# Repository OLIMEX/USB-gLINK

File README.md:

# USB-gLINK

Industrial grade USB LTE cat 4 module optimized for IoT applications with integrated LiPo Battery power supply charger and Navigation.

Product page: https://www.olimex.com/Products/IoT/LTE/USB-gLINK/open-source-hardware

* Works with OLinuXino OSHW Linux Computers, Beaglebone and Raspberry Pi.

* LTE speed 150Mbps downlink and 50Mbps uplink. Backward-compatible with existing EDGE and GSM/GPRS networks.

* Navigation Supports: GPS, GLONASS, BeiDou/Compass, Galileo and QZSS navigation.

* Protocols: TCP / UDP / PPP / FTP / HTTP / NTP / PING / QMI / NITZ / SMTP / MQTT / CMUX / HTTPS / FTPS / SMTPS / SSL / MMS / FILE.

* USB serial drivers for Windows 7/8/8.1/10, Linux and Android.

* Works anywehere in the world: B1 / B2 / B3 / B4 / B5 / B7 / B8 / B12 / B13 / B18 / B19 / B20 / B25 / B26 / B28 / B38 / B39 / B40 / B41.

* Approvals Carrier: Deutsche Telekom (Europe), Verizon/AT&T/Sprint/U.S. Cellular/T-Mobile (North America), Telus/Rogers (Canada)

* Regulatory: GCF (Global), CE (Europe), FCC/PTCRB (North America), IC (Canada), Anatel (Brazil), IFETEL (Mexico), SRRC/CCC/NAL (China), KC (South Korea), NCC (Taiwan, China), JATE/TELEC (Japan), RCM (Australia & New Zealand), FAC (Russia), NBTC (Thailand), IMDA (Singapore), ICASA (South Africa)

## Licensee
* Hardware is released under CERN Open Hardware Licence Version 2 -
Strongly Reciprocal
* Software is released under GPL3 Licensee
* Documentation is released under CC BY-SA 3.0

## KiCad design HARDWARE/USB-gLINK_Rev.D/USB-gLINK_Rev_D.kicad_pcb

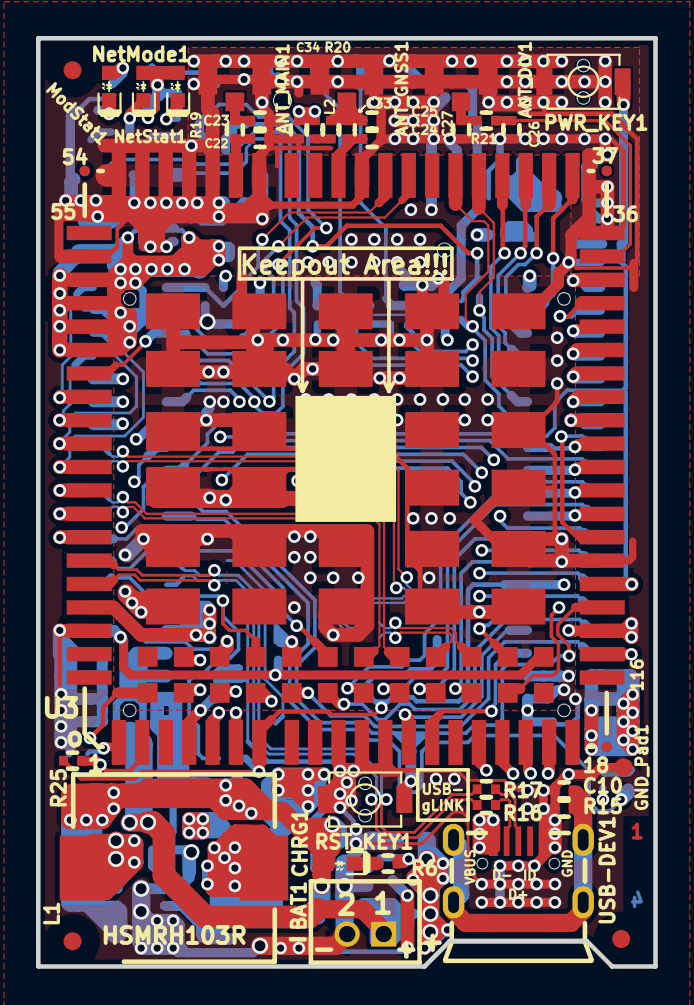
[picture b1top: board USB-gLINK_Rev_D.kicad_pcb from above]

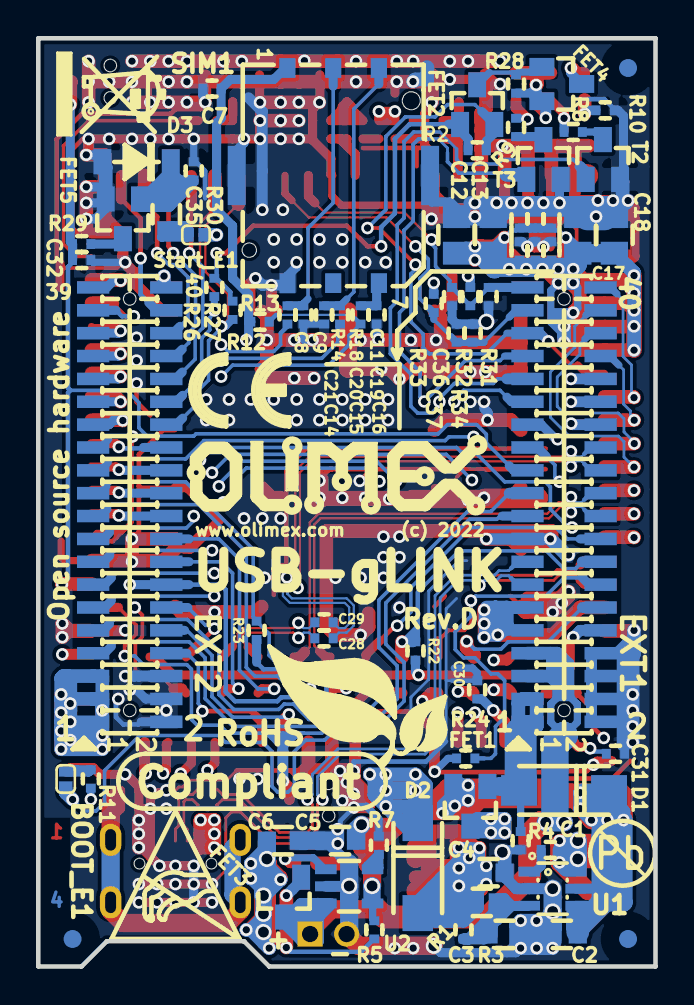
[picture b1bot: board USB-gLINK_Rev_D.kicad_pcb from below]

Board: 4 copper layers, 34.3 x 51.6 mm, 115 parts (80 on the bottom side), 107 nets.

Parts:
ANT_DIV1: NA(U.FL-R-SMT-1); U.FL-R-SMT-1
ANT_GNSS1: (U.FL-R-SMT-1)+(ANTENNA-GPS-25x25-200-u.FL); U.FL-R-SMT-1
ANT_MAIN1: (U.FL-R-SMT-1)+(ANTENNA_GSM_U.FL(PCB)); U.FL-R-SMT-1
BAT1: DW02S; LIPO_BAT_VERTICAL_DW02S
BOOT_E1: Opened; SJ_1_SMALLER
C1, C7, C14, C19, C28, C29, C34: 100nF/10V/10%/X5R/C0402; C_0402_5MIL_DWS
C2, C4, C5, C6, C35: 22uF/6.3V/20%/X5R/C0603; C_0603_5MIL_DWS
C3, C8, C9, C11, C15, C20: 33pF/50V/5%/COG/C0402; C_0402_5MIL_DWS
C10, C30, C31, C32: 10nF/10V/10%/X5R/C0402; C_0402_5MIL_DWS
C12, C13, C17, C18: 47uF/6.3V/20%/X5R/C0805; C_0805_5MIL_DWS
C16, C21: 10pF/50V/5%/COG/C0402; C_0402_5MIL_DWS
C22, C23, C24, C25, C26, C27: NA/C0402; C_0402_5MIL_DWS
C33: 100pF/50V/5%/COG/C0402; C_0402_5MIL_DWS
C36, C37: NA(100nF/10V/10%/X5R/C0402); C_0402_5MIL_DWS
CE_Logo: CE_Sign
CHRG1: LED/Yellow/0603; LED_0603_KA
D1, D2: 1N5822/SMA; SMA-KA
D3: 1N5819S4/SOD123; SOD-123_1C-2A_KA
EXT1, EXT2: NA(YA-V36P-2X20-LF); GPCB127SMT-02X20(YA-V36P-2X20-LF)
FET1, FET3, FET4: IRLML6402(SOT23-3); SOT23
FET2, FET5: BSS138(SOT23-3); SOT23
FID1, FID2, FID3, FID4, FID5, FID6: Fiducial; Fiducial1x3
GND_Pad1: TESTPAD; TESTPAD_40-ROUND
L1: 2.5uH/3.2A/26mR/20%/10.3x10.4x3.0mm(HSMRH103R-2R5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; HSMRH103R
L2: 33nH/0402; L_0402_5MIL_DWS
Logo_OLimeX: OLIMEX_LOGO_TB
Logo_RecycleBin: LOGO_RECYCLEBIN_1
ModStat1: LED/Green/0603; LED_0603_KA
NetMode1: LED/Red/0603; LED_0603_KA
NetStat1: LED/Yellow/0603; LED_0603_KA
PWR_KEY1: IT1185AU2; IT1185AU2_V2
R1: 200k/1%/R0603; R_0603_5MIL_DWS
R2, R4, R5, R12, R28: 10k/R0402; R_0402_5MIL_DWS
R3: 33k/1%/R0603; R_0603_5MIL_DWS
R6, R7, R8, R9, R10: 2.2k/R0402; R_0402_5MIL_DWS
R11: 4.7k/R0402; R_0402_5MIL_DWS
R13, R14, R16, R17, R18: 22R/R0402; R_0402_5MIL_DWS
R15: 1M/R0402; R_0402_5MIL_DWS
R19: 0R/R0402; R_0402_5MIL_DWS
R20: 10R/R0402; R_0402_5MIL_DWS
R21: NA(0R/R0402); R_0402_5MIL_DWS
R22: NA(1.5k/R0402); R_0402_5MIL_DWS
R23, R24, R25, R32: NA(10k/R0402); R_0402_5MIL_DWS
R26, R27: NA(3.9k/R0402); R_0402_5MIL_DWS
R29: 100R/R0402; R_0402_5MIL_DWS
R30: 470k/R0402; R_0402_5MIL_DWS
R31: NA(4.7k/R0402); R_0402_5MIL_DWS
R33: NA(1M/R0402); R_0402_5MIL_DWS
R34: NA(470k/R0402); R_0402_5MIL_DWS
RST_KEY1: IT1185AU2; IT1185AU2_V2
SIM1: SIMNANO-6P-1.3H
Sign_Antistatic: Val**; LOGO_ANTISTATIC_1
Sign_Pb-Free: LOGO_PBFREE
Sign_RoHS: Val**; LOGO_ROHS_1
Start_E1: Soldered; SJ_1_SMALLER
T2, T3: LMUN2211LT1G(SOT23-3); SOT23
U1: SY8113(SOT23-6); SOT23-6
U2: BL4054B-42TPRN(SOT23-5); SOT-23-5
U3: Quectel_EG25-G_Module; Quectel_EG25-G_Module_LGA-144_32.0mmx29.0mmx2.4mm
USB-DEV1: MISB-SWMM-5B-LF(USB_MICRO); USB-MICRO_MISB-SWMM-5B_LF

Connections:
+5V: C2.1, C5.1, CHRG1.2, D1.1, FET1.2, R5.2, R32.2, U1.4, U1.5, U2.4
+5V_EXT: D1.2, EXT1.1, EXT1.3, FET1.1, R4.2
+5V_USB: EXT1.9, EXT1.11, FET1.3, U3.71, USB-DEV1.1
/ADC0: C36.1, EXT1.39, R31.1, R32.1, U3.45
/ADC1: C37.2, EXT1.37, R33.2, R34.1, U3.44
/ANT_PWR: C34.1, FET4.3, ModStat1.2, R20.2
/AP_Ready: EXT1.27, R25.2, U3.2
/BT_CTS: EXT2.32, U3.40
/BT_EN: EXT2.40, U3.139
/BT_RTS: EXT2.38, U3.37
/BT_RxD: EXT2.34, U3.39
/BT_TxD: EXT2.36, U3.38
/COEX_UART_RX: EXT2.18, U3.137
/COEX_UART_TX: EXT2.16, U3.138
/CTS: EXT1.36, U3.64
/DBG_RxD: EXT2.10, U3.11
/DBG_TxD: EXT2.8, U3.12
/DCD: EXT1.34, U3.63
/DTR: EXT1.32, U3.66
/EPHY_INTn: EXT1.14, R24.1, U3.120
/EPHY_RSTn: EXT1.12, U3.119
/I2C_SCL: EXT2.30, R26.2, U3.41
/I2C_SDA: EXT2.28, R27.2, U3.42
/Module_Status: EXT1.35, FET2.2, R2.1, U3.61
/Net_Mode: EXT1.31, T2.1, U3.5
/Net_Status: EXT1.33, T3.1, U3.6
/PCM_CLK: EXT2.26, U3.27
/PCM_IN: EXT2.20, U3.24
/PCM_OUT: EXT2.22, U3.25
/PCM_SYNC: EXT2.24, U3.26
/PM_ENABLE: EXT2.12, U3.127
/PWR_KEY: C32.1, EXT1.23, PWR_KEY1.1, R29.2, U3.21
/RI: EXT1.40, U3.62
/RST_KEY: EXT1.21, RST_KEY1.1, U3.20
/RTS: EXT1.38, U3.65
/RxD: EXT1.28, U3.68
/SDC1_CLK: EXT2.7, U3.133
/SDC1_CMD: EXT2.9, U3.134
/SDC1_DATA0: EXT2.11, U3.132
/SDC1_DATA1: EXT2.13, U3.131
/SDC1_DATA2: EXT2.15, U3.130
/SDC1_DATA3: EXT2.17, U3.129
/SDC2_CLK: EXT2.35, U3.32
/SDC2_CMD: EXT2.37, U3.33
/SDC2_DATA0: EXT2.33, U3.31
/SDC2_DATA1: EXT2.31, U3.30
/SDC2_DATA2: EXT2.29, U3.29
/SDC2_DATA3: EXT2.27, U3.28
/SD_INS_DET#: EXT2.25, U3.23
/SGMII_MCLK: EXT1.18, U3.122
/SGMII_MDATA: EXT1.16, R22.1, U3.121
/SGMII_RX+: C28.2, U3.125
/SGMII_RX-: C29.2, U3.126
/SGMII_RX_N: C29.1, EXT1.26
/SGMII_RX_P: C28.1, EXT1.24
/SGMII_TX_N: EXT1.20, U3.123
/SGMII_TX_P: EXT1.22, U3.124
/SIM_CLK: R14.1, U3.16
/SIM_DATA: R12.1, R18.1, U3.15
/SIM_RST: R13.1, U3.17
/SIM_VDD: C7.2, R12.2, SIM1.1, U3.14
/TxD: EXT1.30, U3.67
/USB-D_N: EXT1.13, R16.1, U3.70
/USB-D_P: EXT1.15, R17.1, U3.69
/USB_BOOT: BOOT_E1.2, EXT1.19, U3.115
/USB_D+: R17.2, USB-DEV1.3
/USB_D-: R16.2, USB-DEV1.2
/USIM2_VDD: EXT1.10, R22.2, U3.128
/VDD-SDIO: EXT2.39, U3.34
/VDD_EXT: EXT2.14, FET2.1, R2.2, R11.1, R23.1, R24.2, R25.1, R26.1, R27.1, U3.7
/WAKE_ON_WIRELESS: EXT2.21, R23.2, U3.135
/WLAN_EN: EXT2.19, U3.136
/WLAN_SLP_CLK: EXT2.23, U3.118
/W_Disable: C30.1, EXT1.29, U3.4
/Wakeup_In: C31.1, EXT1.25, U3.1
GND: ANT_DIV1.2, ANT_GNSS1.2, ANT_MAIN1.2, BAT1.2, C2.2, C4.2, C5.2, C6.2, C7.1, C8.2, C9.2, C10.2, C11.2, C12.2, C13.2, C14.2, C15.2, C16.2, C17.2, C18.2, C19.2, C20.2, C21.2, C22.1, C23.1, C24.1, C25.1, C26.1, C27.1, C30.2, C31.2, C32.2, C34.2, C36.2, C37.1, D3.2, EXT1.2, EXT1.4, EXT1.6, EXT1.8, EXT1.17, EXT2.2, EXT2.4, EXT2.6, FET5.2, GND_Pad1.1, PWR_KEY1.2, R3.2, R4.1, R7.2, R10.2, R15.2, R30.1, R31.2, R34.2, RST_KEY1.2, SIM1.0, SIM1.5, T2.2, T3.2, U1.2, U2.2, U3.8, U3.9, U3.10, U3.19, U3.22, U3.36, U3.46, U3.48, U3.50, U3.51, U3.52, U3.53, U3.54, U3.56, U3.72, U3.85, U3.86, U3.87, U3.88, U3.89, U3.90, U3.91, U3.92, U3.93, U3.94, U3.95, U3.96, U3.97, U3.98, U3.99, U3.100, U3.101, U3.102, U3.103, U3.104, U3.105, U3.106, U3.107, U3.108, U3.109, U3.110, U3.111, U3.112, USB-DEV1.5
unnamed: ANT_DIV1.1, C27.2, R21.1
unnamed: ANT_GNSS1.1, C25.2, C33.2, L2.2
unnamed: ANT_MAIN1.1, C23.2, R19.1
unnamed: BOOT_E1.1, R11.2
unnamed: C1.1, U1.1
unnamed: C1.2, L1.1, U1.6
unnamed: C3.1, R1.1, R3.1, U1.3
unnamed: C3.2, C4.1, D2.2, L1.2, R1.2
unnamed: C8.1, R13.2, SIM1.2
unnamed: C9.1, R14.2, SIM1.3
unnamed: C10.1, R15.1, USB-DEV1.0
unnamed: C11.1, R18.2, SIM1.7
unnamed: C22.2, R19.2, U3.49
unnamed: C24.2, C33.1, U3.47
unnamed: C26.2, R21.2, U3.35
unnamed: C35.1, Start_E1.2
unnamed: C35.2, D3.1, FET5.1, R30.2
unnamed: CHRG1.1, R6.1
unnamed: FET2.3, FET4.1, R28.2
unnamed: FET3.1, R5.1
unnamed: FET5.3, R29.1
unnamed: L2.1, R20.1
unnamed: ModStat1.1, R10.1
unnamed: NetMode1.1, R8.1
unnamed: NetStat1.1, R9.1
unnamed: R6.2, U2.1
unnamed: R7.1, U2.5
unnamed: R8.2, T2.3
unnamed: R9.2, T3.3
VBAT: BAT1.1, EXT1.5, EXT1.7, FET3.3, R33.1, U2.3
VDD: C6.1, C12.1, C13.1, C14.1, C15.1, C16.1, C17.1, C18.1, C19.1, C20.1, C21.1, D2.1, EXT2.1, EXT2.3, EXT2.5, FET3.2, FET4.2, NetMode1.2, NetStat1.2, R28.1, Start_E1.1, U3.57, U3.58, U3.59, U3.60

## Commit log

2020-04-28 initial upload CAD and docs
2020-04-28 user manual
2024-11-07 Update
    Hardware revision D
2024-11-07 Update
    Latest hardware revision

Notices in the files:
HARDWARE/USB-gLINK_Rev.D/USB-gLINK_Rev_D.kicad_pcb:
www.olimex.com (c) 2022
